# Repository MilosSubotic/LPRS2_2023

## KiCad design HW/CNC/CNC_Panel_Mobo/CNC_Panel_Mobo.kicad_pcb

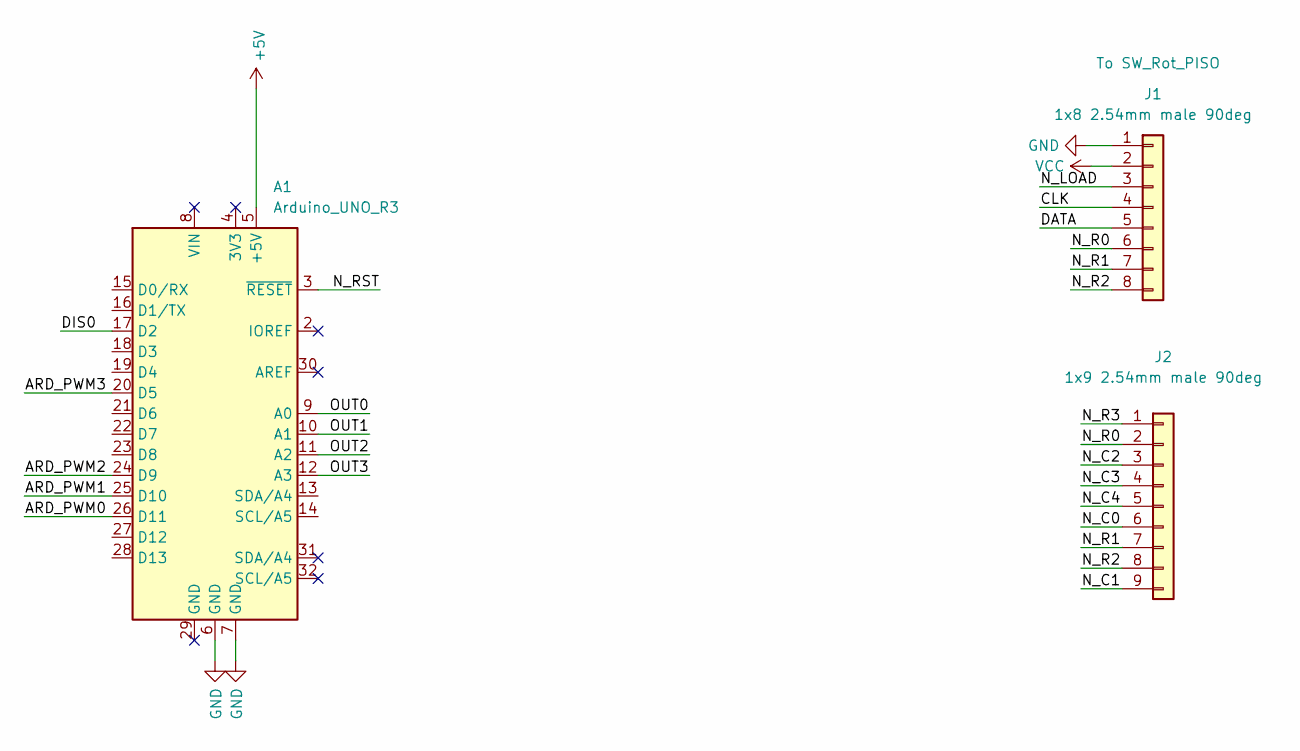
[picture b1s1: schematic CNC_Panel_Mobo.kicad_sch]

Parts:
A1: Arduino_UNO_R3; Arduino_UNO_R3_WithMountingHoles_Snapped_to_P2.54mm
J1: 1x8 2.54mm male 90deg; PinHeader_1x08_P2.54mm_Vertical
J2: 1x9 2.54mm male 90deg; PinHeader_1x09_P2.54mm_Vertical

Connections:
+5V: A1.5 (+5V)
/ARD_PWM0: A1.26 (D11)
/ARD_PWM1: A1.25 (D10)
/ARD_PWM2: A1.24 (D9)
/ARD_PWM3: A1.20 (D5)
/CLK: J1.4
/DATA: J1.5
/DIS0: A1.17 (D2)
/N_C0: J2.6
/N_C1: J2.9
/N_C2: J2.3
/N_C3: J2.4
/N_C4: J2.5
/N_LOAD: J1.3
/N_R0: J1.6, J2.2
/N_R1: J1.7, J2.7
/N_R2: J1.8, J2.8
/N_R3: J2.1
/N_RST: A1.3 (~RESET)
/OUT0: A1.9 (A0)
/OUT1: A1.10 (A1)
/OUT2: A1.11 (A2)
/OUT3: A1.12 (A3)
GND: A1.6 (GND), A1.7 (GND), J1.1
VCC: J1.2

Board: 2 copper layers, 3 parts (0 on the bottom side), 4 nets, no tracks yet.

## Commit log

2023-06-14 Finished other holes.
2023-06-14 Adding PBs.
2023-06-14 Another HW prj.
2023-06-15 Finished PCB.
2023-06-16 New prj.
2023-06-16 Moving.
2023-06-16 Correction
2023-06-16 Renaming. Hale all prjs.
